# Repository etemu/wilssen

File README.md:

wilssen
=======

Wireless / Wind Logging System for Sourcing ENergy - "Wilssen" is a modular controller for e.g. a wind turbine, it monitors all parameters like phase voltage and efficiency when the wind turbine is generating power.

Compatible with the the Arduino platform.

CC-BY-SA 3.0: This work is Open Source and licensed under
the Creative Commons Attribution-ShareAlike 3.0 License.

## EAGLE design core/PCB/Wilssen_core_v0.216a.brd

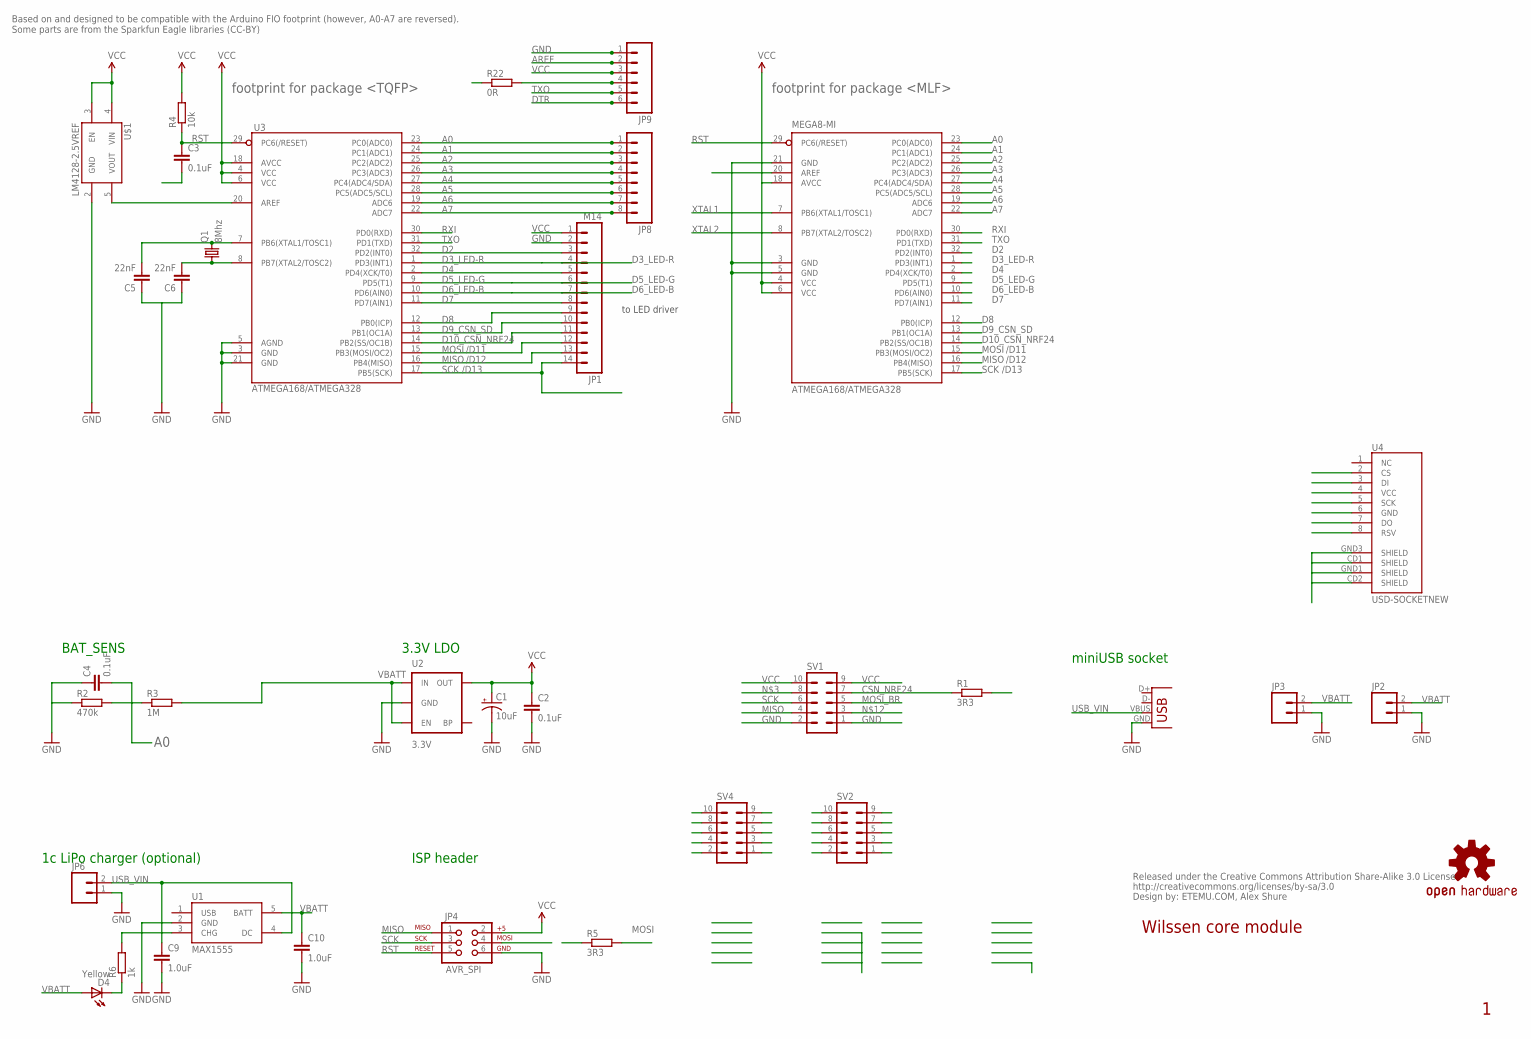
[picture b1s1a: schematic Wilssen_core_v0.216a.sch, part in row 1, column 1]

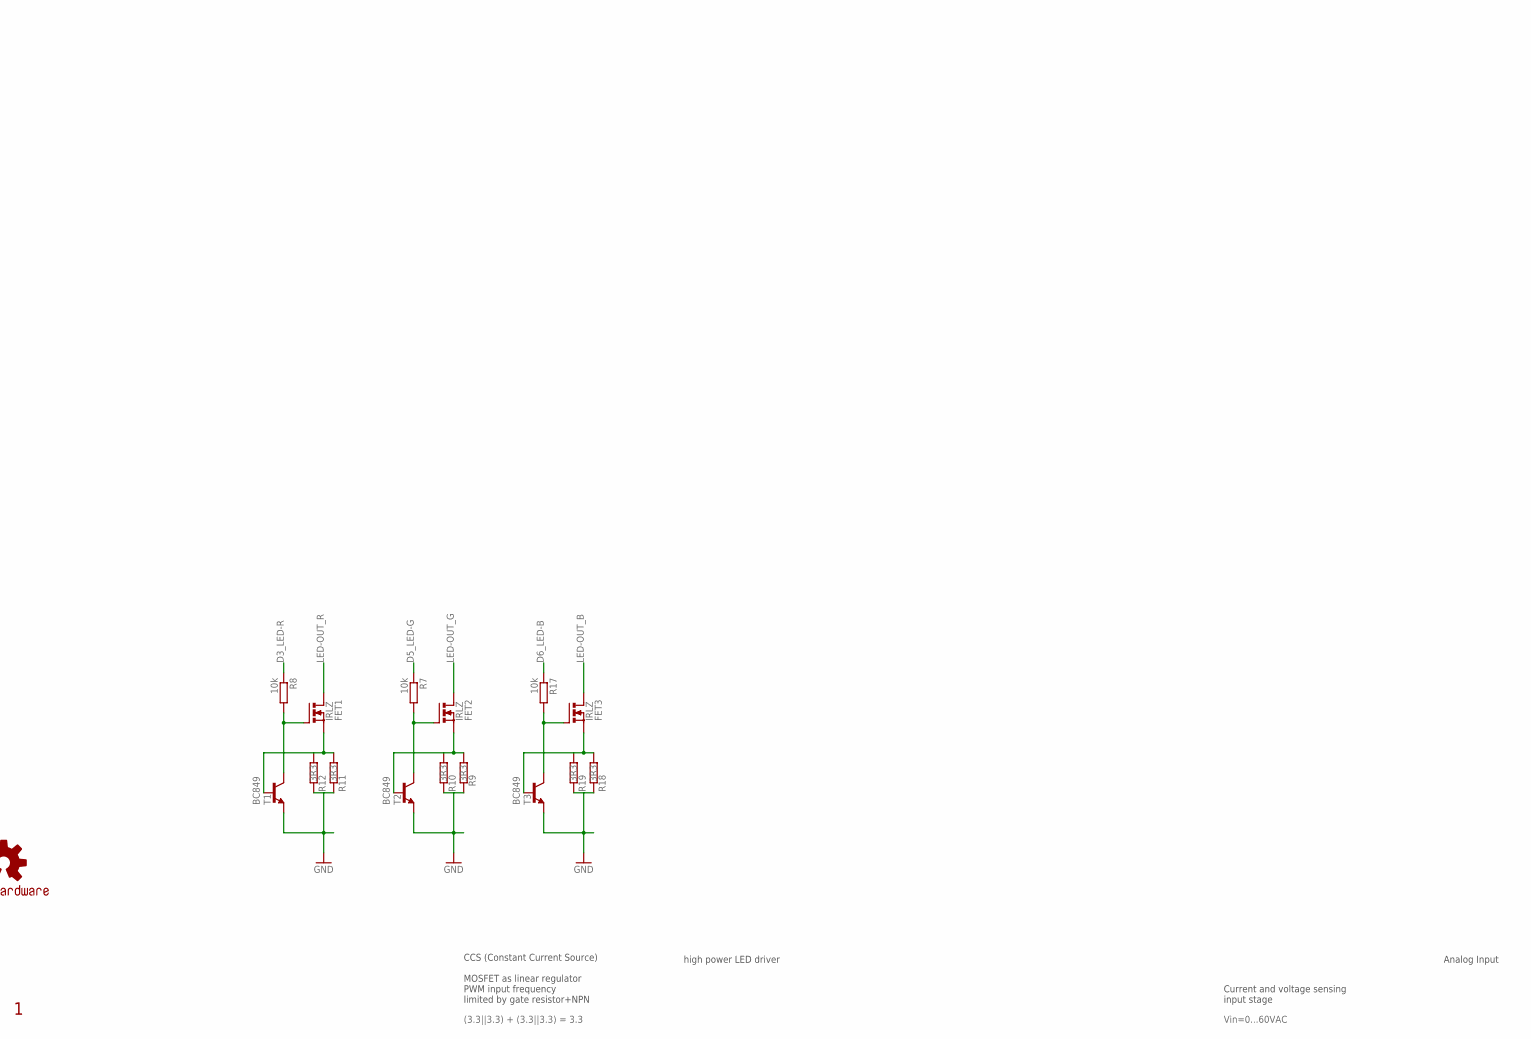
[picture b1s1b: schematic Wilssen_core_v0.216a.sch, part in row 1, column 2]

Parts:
ATMEGA168/ATMEGA328: MEGA8-MI; MLF32
C1: 10uF; EIA3216
C2, C3, C4: 0.1uF; 0805
C5, C6: 22nF; 0805
C9, C10: 1.0uF; 0805
CC_TEXT1: CREATIVE_COMMONS
D4: Yellow; LED-0603
FET1, FET2, FET3: IRLZ; TO220BV
JP1: M14; 1X14
JP2, JP6: M02PTH; 1X02
JP3: M02-JST-2MM-SMT; S2B-PH
JP4: AVR_SPI; 2X3
JP8: M081X08; 1X08
JP9: M06SIP; 1X06
LOGO3: OSHW-LOGOS; OSHW-LOGO-S
Q1: 8Mhz; SM49
R1, R5, R9, R10, R11, R12, R18, R19: 3R3; R1206
R2: 470k; R0805
R3: 1M; R0805
R4, R7, R8, R17: 10k; R0805
R6: 1k; R0805
R22: 0R; R1206
SV1, SV2, SV4: MA05-2
T1, T2, T3: BC849; SOT23
U1: MAX1555; SOT23-5
U2: 3.3V; SOT23-5
U3: ATMEGA168/ATMEGA328; TQFP32-08
U4: USD-SOCKETNEW; MICRO-SD-SOCKET-PP
U$1: LM4128-2.5VREF; SOT23-5
X1: USBSMD; USB-MINIB

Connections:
A0: ATMEGA168/ATMEGA328.23 (PC0(ADC0)), C4.2, JP8.1, R2.2, R3.1, U3.23 (PC0(ADC0))
A1: ATMEGA168/ATMEGA328.24 (PC1(ADC1)), JP8.2, U3.24 (PC1(ADC1))
A2: ATMEGA168/ATMEGA328.25 (PC2(ADC2)), JP8.3, U3.25 (PC2(ADC2))
A3: ATMEGA168/ATMEGA328.26 (PC3(ADC3)), JP8.4, U3.26 (PC3(ADC3))
A4: ATMEGA168/ATMEGA328.27 (PC4(ADC4/SDA)), JP8.5, U3.27 (PC4(ADC4/SDA))
A5: ATMEGA168/ATMEGA328.28 (PC5(ADC5/SCL)), JP8.6, U3.28 (PC5(ADC5/SCL))
A6: ATMEGA168/ATMEGA328.19 (ADC6), JP8.7, U3.19 (ADC6)
A7: ATMEGA168/ATMEGA328.22 (ADC7), JP8.8, U3.22 (ADC7)
AREF: ATMEGA168/ATMEGA328.20 (AREF), JP9.2, U3.20 (AREF), U$1.5 (VOUT)
CSN: SV2.8, SV4.8
CSN_NRF24: R1.1, SV1.7
D2: ATMEGA168/ATMEGA328.32 (PD2(INT0)), JP1.3, U3.32 (PD2(INT0))
D3_LED-R: ATMEGA168/ATMEGA328.1 (PD3(INT1)), JP1.4, R8.1, U3.1 (PD3(INT1))
D4: ATMEGA168/ATMEGA328.2 (PD4(XCK/T0)), JP1.5, U3.2 (PD4(XCK/T0))
D5_LED-G: ATMEGA168/ATMEGA328.9 (PD5(T1)), JP1.6, R7.1, U3.9 (PD5(T1))
D6_LED-B: ATMEGA168/ATMEGA328.10 (PD6(AIN0)), JP1.7, R17.1, U3.10 (PD6(AIN0))
D7: ATMEGA168/ATMEGA328.11 (PD7(AIN1)), JP1.8, U3.11 (PD7(AIN1))
D8: ATMEGA168/ATMEGA328.12 (PB0(ICP)), JP1.9, U3.12 (PB0(ICP))
D9_CSN_SD: ATMEGA168/ATMEGA328.13 (PB1(OC1A)), JP1.10, U3.13 (PB1(OC1A)), U4.2 (CS)
D10_CSN_NRF24: ATMEGA168/ATMEGA328.14 (PB2(SS/OC1B)), JP1.11, R1.2, U3.14 (PB2(SS/OC1B))
DTR: C3.2, JP9.6
GATE1: FET1.G, R8.2, T1.3 (C)
GATE2: FET2.G, R7.2, T2.3 (C)
GATE3: FET3.G, R17.2, T3.3 (C)
GND: ATMEGA168/ATMEGA328.3 (GND), ATMEGA168/ATMEGA328.5 (GND), ATMEGA168/ATMEGA328.21 (GND), C1.C (-), C2.2, C4.1, C5.1, C6.1, C9.2, C10.2, JP1.2, JP2.1, JP3.1, JP4.6, JP6.1, JP9.1, R2.1, R9.2, R10.2, R11.2, R12.2, R18.2, R19.2, SV1.1, SV1.2, SV4.1, SV4.3, SV4.5, SV4.7, T1.2 (E), T2.2 (E), T3.2 (E), U1.2 (GND), U2.2 (GND), U3.3 (GND), U3.5 (AGND), U3.21 (GND), U4.6 (GND), U4.CD1 (SHIELD), U4.CD2 (SHIELD), U4.GND1 (SHIELD), U4.GND3 (SHIELD), U$1.2 (GND), X1.GND
LED-OUT_B: FET3.D
LED-OUT_G: FET2.D
LED-OUT_R: FET1.D
MISO: ATMEGA168/ATMEGA328.16 (PB4(MISO)), JP1.13, JP4.1, SV1.4, SV2.2, SV4.2, U3.16 (PB4(MISO))
MOSI: ATMEGA168/ATMEGA328.15 (PB3(MOSI/OC2)), JP1.12, JP4.4, R5.2, SV2.10, SV4.10, U3.15 (PB3(MOSI/OC2))
MOSI_BR: SV1.5
unnamed: D4.C, R6.1
unnamed: R6.2, U1.3 (CHG)
RST: ATMEGA168/ATMEGA328.29 (PC6(/RESET)), C3.1, JP4.5, R4.1, SV2.6, SV4.6, U3.29 (PC6(/RESET))
RXI: ATMEGA168/ATMEGA328.30 (PD0(RXD)), R22.1, U3.30 (PD0(RXD))
RXI_CON: JP9.4, R22.2
SCK: ATMEGA168/ATMEGA328.17 (PB5(SCK)), JP1.14, JP4.3, SV1.6, SV2.4, SV4.4, U3.17 (PB5(SCK)), U4.5 (SCK)
SRC1: FET1.S, R11.1, R12.1, T1.1 (B)
SRC2: FET2.S, R9.1, R10.1, T2.1 (B)
SRC3: FET3.S, R18.1, R19.1, T3.1 (B)
TXO: ATMEGA168/ATMEGA328.31 (PD1(TXD)), JP9.5, U3.31 (PD1(TXD))
USB_VIN: C9.1, JP6.2, U1.4 (DC), X1.VBUS
VBATT: C10.1, D4.A, JP2.2, JP3.2, R3.2, U1.5 (BATT), U2.1 (IN), U2.3 (EN)
VCC: ATMEGA168/ATMEGA328.4 (VCC), ATMEGA168/ATMEGA328.6 (VCC), ATMEGA168/ATMEGA328.18 (AVCC), C1.A (+), C2.1, JP1.1, JP4.2, JP9.3, R4.2, SV1.9, SV1.10, SV4.9, U2.5 (OUT), U3.4 (VCC), U3.6 (VCC), U3.18 (AVCC), U4.4 (VCC), U$1.3 (EN), U$1.4 (VIN)
XTAL1: ATMEGA168/ATMEGA328.7 (PB6(XTAL1/TOSC1)), C5.2, Q1.2, U3.7 (PB6(XTAL1/TOSC1))
XTAL2: ATMEGA168/ATMEGA328.8 (PB7(XTAL2/TOSC2)), C6.2, Q1.1, U3.8 (PB7(XTAL2/TOSC2))

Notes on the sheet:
Wilssen core module
/D11
/D12
/D13
Based on and designed to be compatible with the Arduino FIO footprint (however, A0-A7 are reversed). Some parts are from the Sparkfun Eagle libraries (CC-BY)
ETEMU.COM, Alex Shure
footprint for package <TQFP>
footprint for package <MLF>
1c LiPo charger (optional)
ISP header
3.3V LDO
BAT_SENS
miniUSB socket
(3.3||3.3) + (3.3||3.3) = 3.3
CCS (Constant Current Source) MOSFET as linear regulator PWM input frequency limited by gate resistor+NPN
high power LED driver
to LED driver
Vin=0...60VAC
Current and voltage sensing input stage
Analog Input

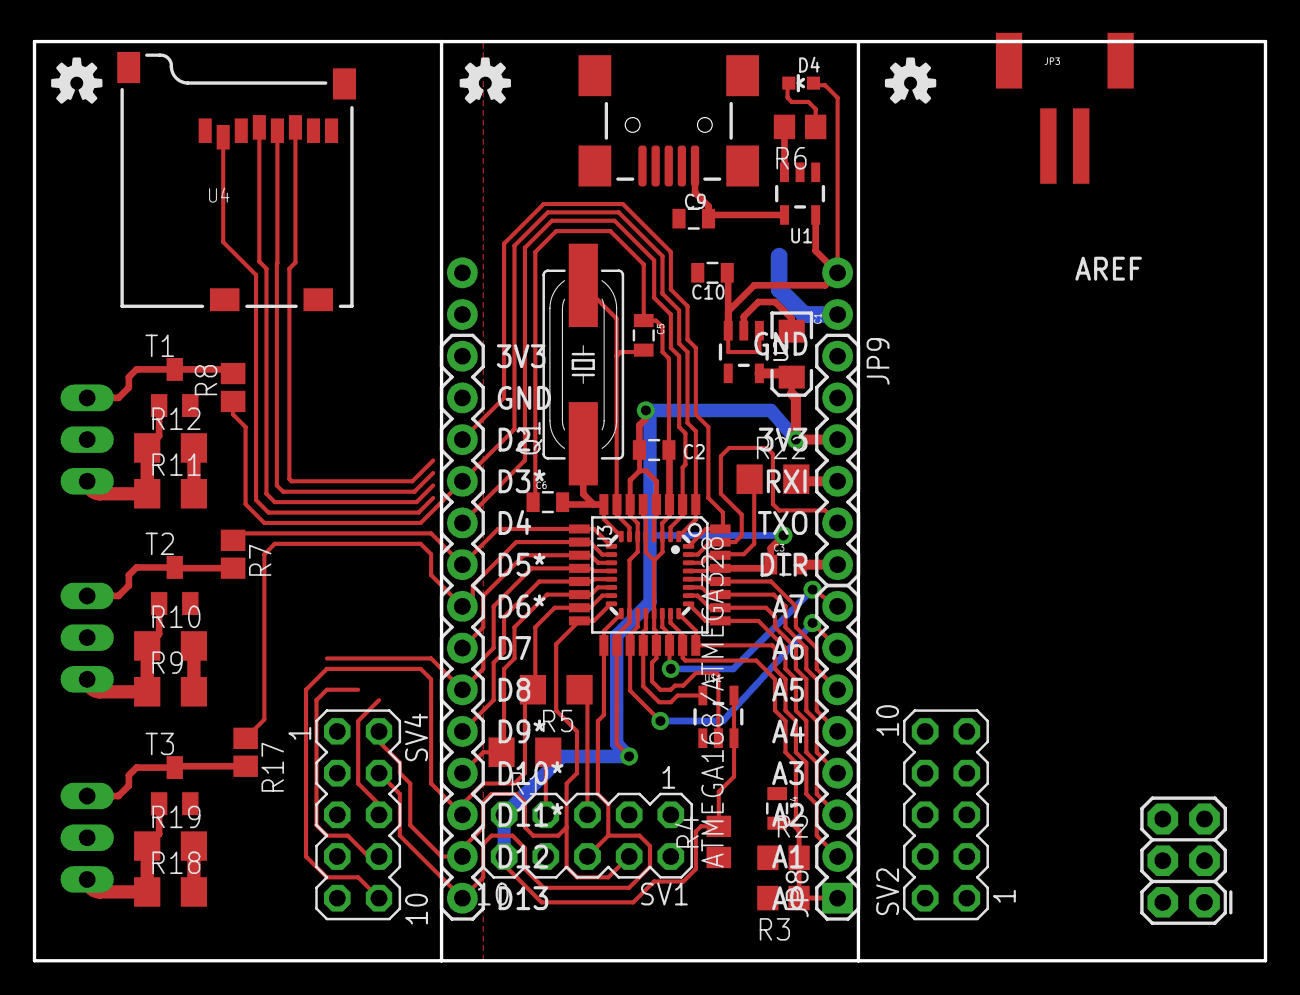
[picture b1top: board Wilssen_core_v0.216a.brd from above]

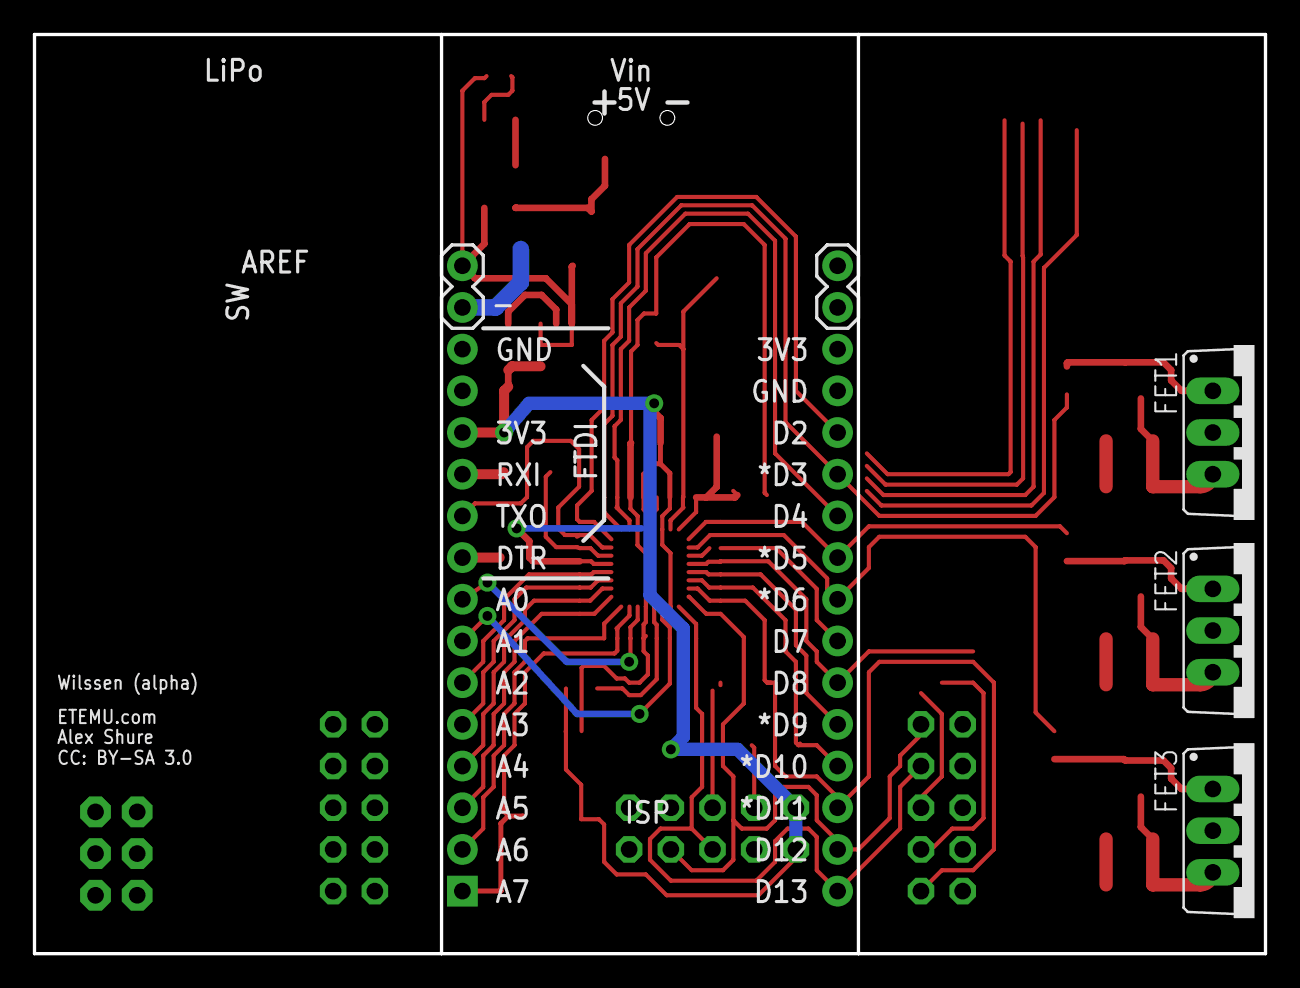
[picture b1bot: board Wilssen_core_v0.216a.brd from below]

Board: 2 copper layers, 75.0 x 56.0 mm, 53 parts (5 on the bottom side), 42 nets.

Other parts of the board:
LOGO1, LOGO2: OSHW-LOGOS; OSHW-LOGO-S

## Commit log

2012-11-28 first sketch of the schematic
2012-11-28 fixed formatting of README
2012-11-28 v0.201a upload (work in progress!)
2012-11-29 added external voltage reference
2012-11-29 added standard .gitignore
2012-12-04 moved eagle files to /PCB
2012-12-05 2.5V voltage reference + tidy up
2012-12-05 added constant current source
    CCS (high brightness LED driver)
2012-12-05 CCS2 added
2012-12-05 v0.203a - high power LED driver integrated
2012-12-05 PNG export
2012-12-05 added the RGBlink Arduino Library
2012-12-05 added comments
2012-12-06 pins have to be PWM compatible
2012-12-07 added blinking
2012-12-09 added soft blinking/examples
2012-12-09 fixed examples
2012-12-09 HSB_to_RGB function added
2012-12-09 added RGB type and better memory management
2012-12-11 implemented hsb
2012-12-11 HSB now working
2012-12-11 cleanup
2012-12-11 v0.204a - rerouted the SMD crystal
    smashed symmetrical layout :-(
    too hard to maintain, too many vias with the symmetry
2012-12-11 NRF24 header added, ICSP rerouting started
2012-12-12 switched to 10 pin ICSP, began to label microSD
2012-12-12 3V3 LDO routed
2012-12-12 added invert option for low-pwm led drivers
2012-12-13 shrunk board size to under 60mm height
    circumvent xtal to eliminate 2 vias.
2012-12-13 power supply rerouted + started to use bottom layer
2012-12-14 added selftest + minor fixes
2012-12-15 fixed failed commit
2012-12-16 added communication
2012-12-16 restructured text
2012-12-22 arduino checksum code
2013-01-09 Create 3.3V LDO regulator
    We are looking for a cheap 3.3 V LDO regulator:
    Must have:
    -low idle current for sleep/standby mode
    -low Vdrop for usage with a 1c LiPo battery as a power supply (3.6-4.2V)
    -Vdrop of 0.4V would be nice.
2013-01-09 Update 3.3V LDO regulator
2013-01-10 added hardware folder
2013-01-11 Update hardware/3.3V LDO regulator
    Added some more regulators
2013-01-15 added basic datalogging
2013-02-04 added docs
2013-02-05 Create client.ino
    Arduino nRf Temperature sensor with fancy blinking lights
2013-02-24 added nodeconfig
2013-03-05 #YOLO
    You only commit once?
2013-03-10 updated timesync
2013-04-04 new update rate calc + NRF24 SPI pinout
    SPI connection changed to CSN at pin 9 and CE at pin 8.
    update rate approx 20k/s
2013-04-05 Microsecond timing and proper verbose serial msgs
2013-05-23 timesync debugging
2013-05-26 forked 'timesync' to 'communication'
    communication is an approach for the general com in addition to the
    timesync
2013-09-14 wip led remote control
2013-09-28 Implemented wireless LED control
    up to 8 RGB LEDs simultaneously
2013-09-29 wip implement EEPROM config
2013-09-29 wip LED patterns
2013-09-29 node EEPROM config endianess fix
2013-10-01 wip mass deployment
2013-10-01 strobe all active node LEDs
2013-10-19 make debug output optional with DEBUG
2013-11-05 make KEEPALIVE optional, wip implement switchcube
2013-11-05 m cleanup
2013-11-05 outsource LED patterns to led_patterns file
2013-11-05 fix integer overflow in updates
2013-11-06 m testing
2013-11-06 push switchcube project from local repo
2013-11-08 hackathon update :+1:
2014-03-01 custom bootloader boards.txt for Arduino IDE
2014-06-14 additional parameter in EEPROM for network role

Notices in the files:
parts and their libraries:
SparkFun-Connectors: Licensing: CC v3.0 Share-Alike You are welcome to use this library for commercial purposes.
SparkFun-Aesthetics: Released under the Creative Commons Attribution Share-Alike 3.0 License
SparkFun-Aesthetics: http://creativecommons.org/licenses/by-sa/3.0
